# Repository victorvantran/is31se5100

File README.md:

# is31se5100
Interfacing multiple is31se5100 with multiple max7301 daisy-chained
Testing different electrodes

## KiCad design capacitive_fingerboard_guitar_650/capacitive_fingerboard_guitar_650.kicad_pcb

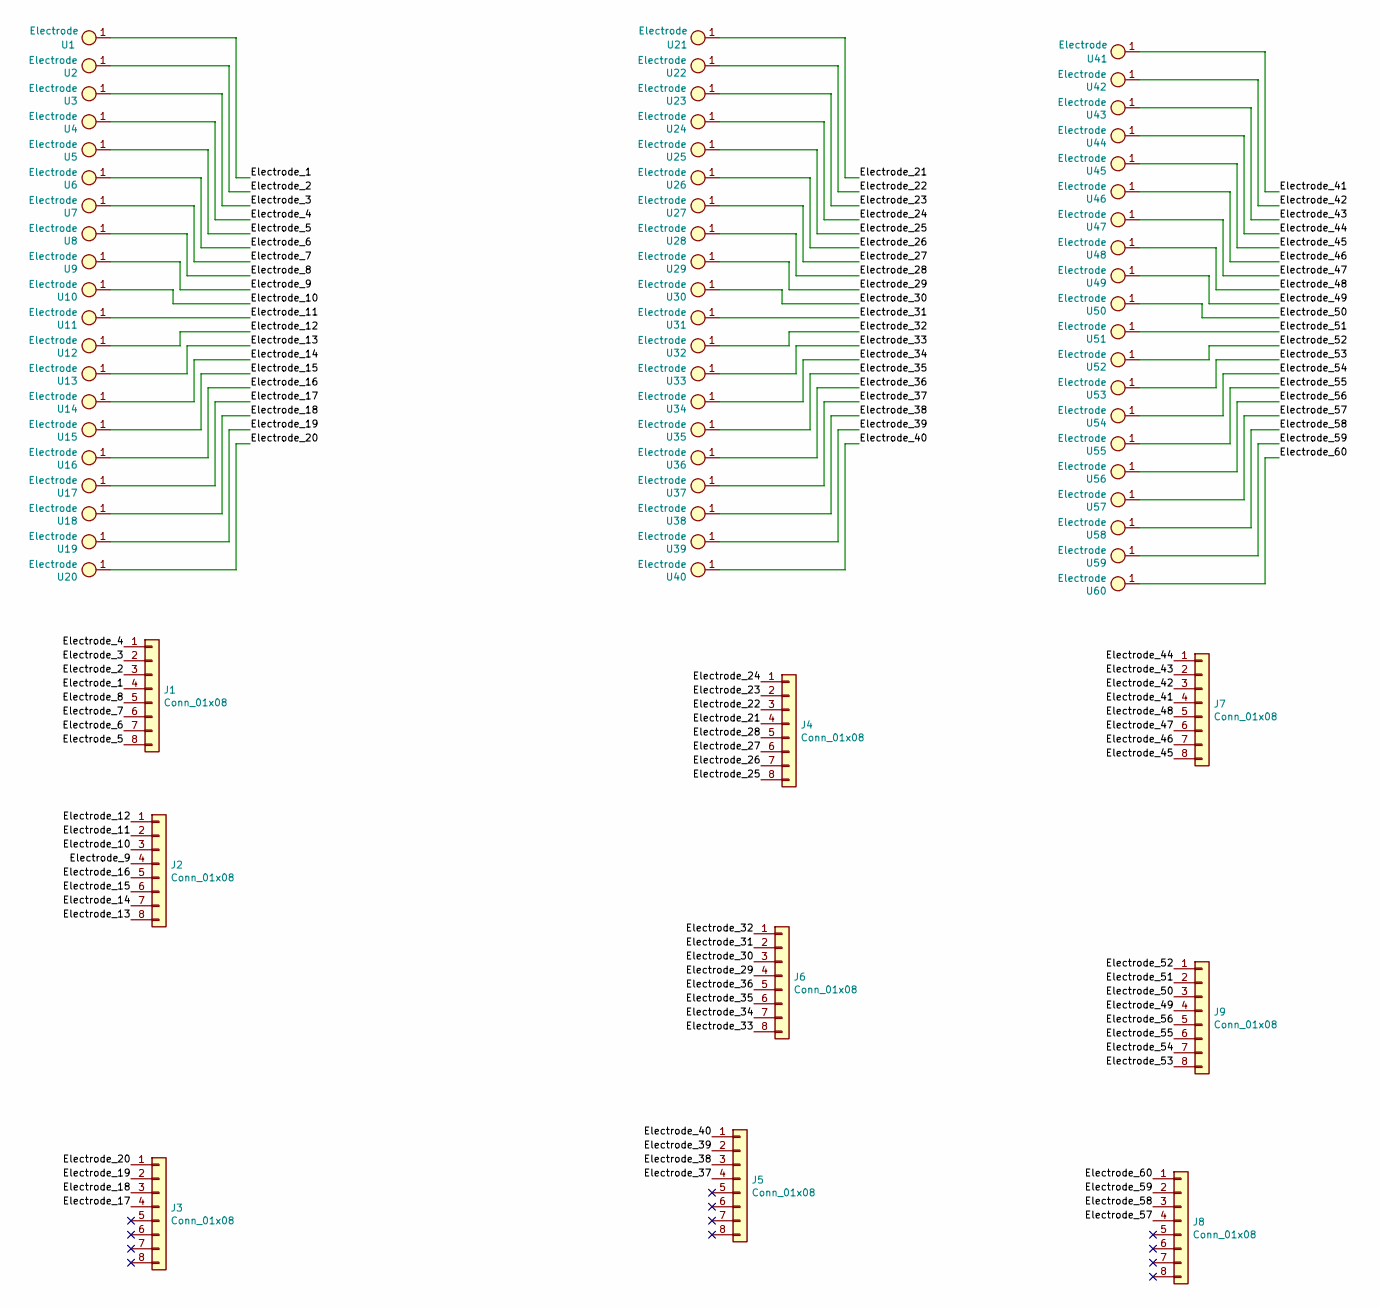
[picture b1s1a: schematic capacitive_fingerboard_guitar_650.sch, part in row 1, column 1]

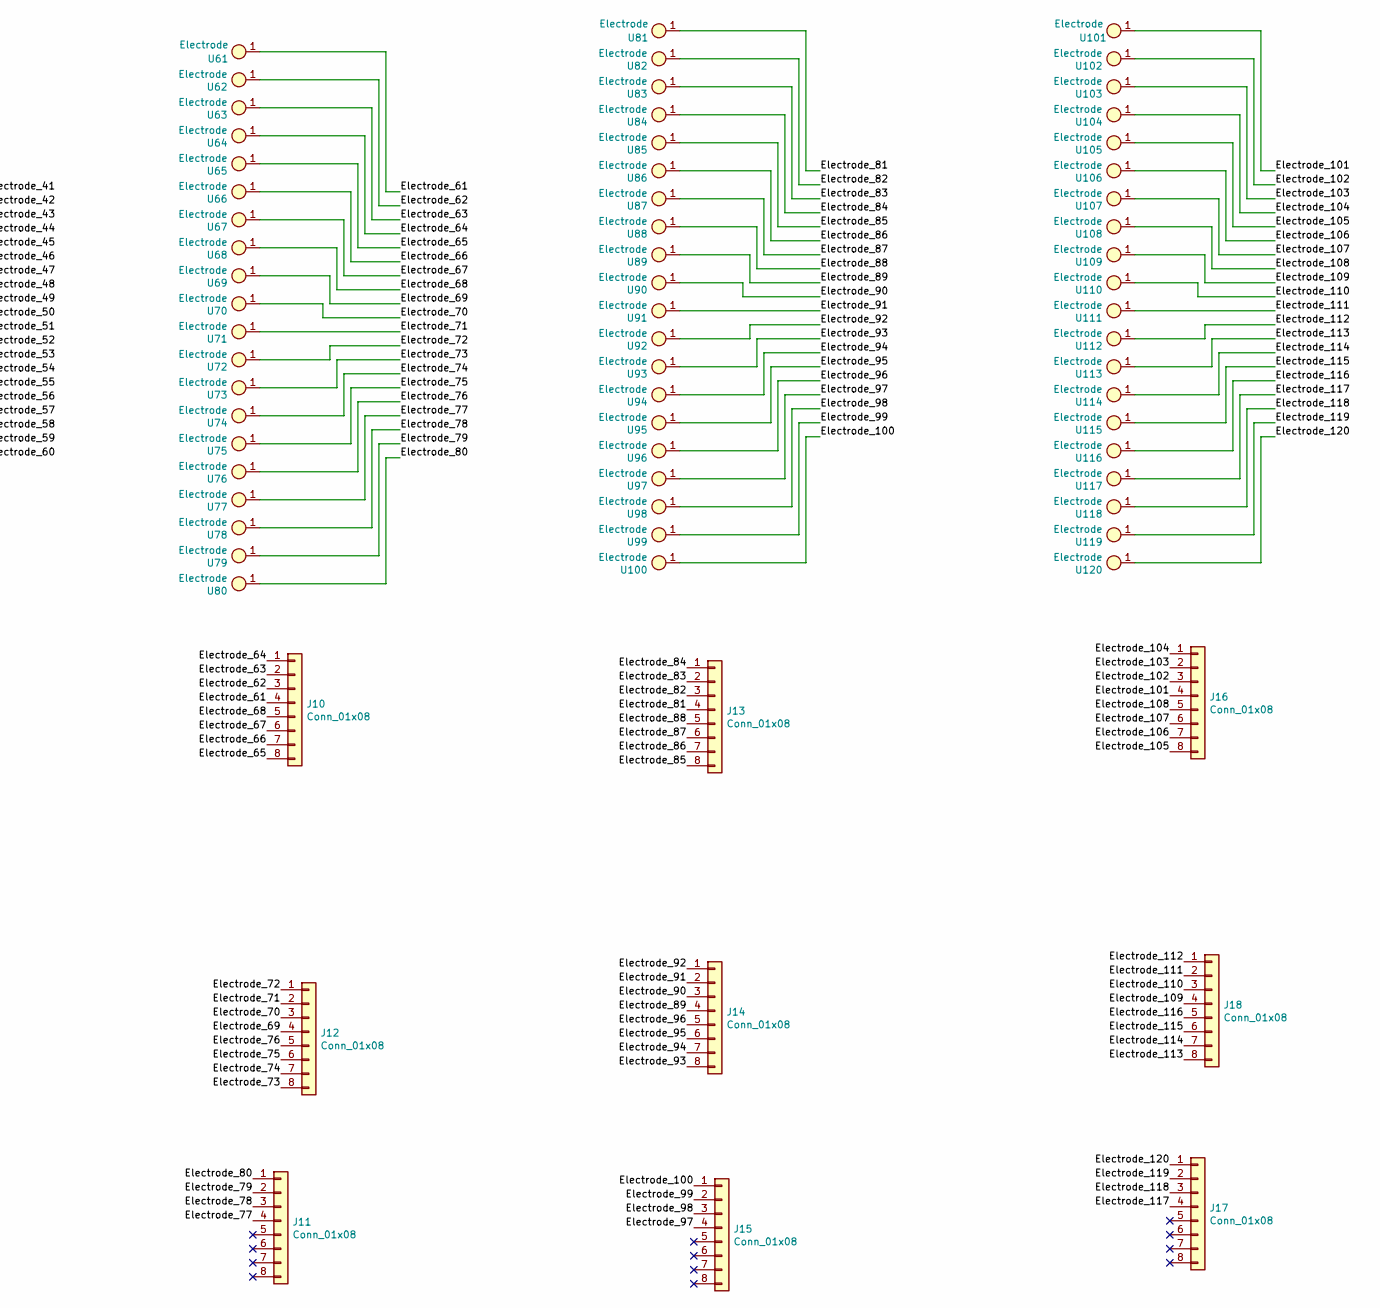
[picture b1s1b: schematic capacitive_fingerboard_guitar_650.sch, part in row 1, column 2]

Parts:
J1, J2, J3, J4, J5, J6, J7, J8, J9, J10, J11, J12, J13, J14, J15, J16, J17, J18: Conn_01x08; SAMTEC_TSM-108-01-F-SV
U1: Electrode; E2_F2
U2: Electrode; E2_F#2
U3: Electrode; E2_G2
U4: Electrode; E2_G#2
U5: Electrode; E2_A2
U6: Electrode; E2_A#2
U7: Electrode; E2_B2
U8: Electrode; E2_C3
U9: Electrode; E2_C#3
U10: Electrode; E2_D3
U11: Electrode; E2_D#3
U12: Electrode; E2_E3
U13: Electrode; E2_F3
U14: Electrode; E2_F#3
U15: Electrode; E2_G3
U16: Electrode; E2_G#3
U17: Electrode; E2_A3
U18: Electrode; E2_A#3
U19: Electrode; E2_B3
U20: Electrode; E2_C4
U21: Electrode; A2_A#2
U22: Electrode; A2_B2
U23: Electrode; A2_C3
U24: Electrode; A2_C#3
U25: Electrode; A2_D3
U26: Electrode; A2_D#3
U27: Electrode; A2_E3
U28: Electrode; A2_F3
U29: Electrode; A2_F#3
U30: Electrode; A2_G3
U31: Electrode; A2_G#3
U32: Electrode; A2_A3
U33: Electrode; A2_A#3
U34: Electrode; A2_B3
U35: Electrode; A2_C4
U36: Electrode; A2_C#4
U37: Electrode; A2_D4
U38: Electrode; A2_D#4
U39: Electrode; A2_E4
U40: Electrode; A2_F4
U41: Electrode; D3_D#3
U42: Electrode; D3_E3
U43: Electrode; D3_F3
U44: Electrode; D3_F#3
U45: Electrode; D3_G3
U46: Electrode; D3_G#3
U47: Electrode; D3_A3
U48: Electrode; D3_A#3
U49: Electrode; D3_B3
U50: Electrode; D3_C4
U51: Electrode; D3_C#4
U52: Electrode; D3_D4
U53: Electrode; D3_D#4
U54: Electrode; D3_E4
U55: Electrode; D3_F4
U56: Electrode; D3_F#4
U57: Electrode; D3_G4
U58: Electrode; D3_G#4
U59: Electrode; D3_A4
U60: Electrode; D3_A#4
U61: Electrode; G3_G#3
U62: Electrode; G3_A3
U63: Electrode; G3_A#3
U64: Electrode; G3_B3
U65: Electrode; G3_C4
U66: Electrode; G3_C#4
U67: Electrode; G3_D4
U68: Electrode; G3_D#4
U69: Electrode; G3_E4
U70: Electrode; G3_F4
U71: Electrode; G3_F#4
U72: Electrode; G3_G4
U73: Electrode; G3_G#4
U74: Electrode; G3_A4
U75: Electrode; G3_A#4
U76: Electrode; G3_B4
U77: Electrode; G3_C5
U78: Electrode; G3_C#5
U79: Electrode; G3_D5
U80: Electrode; G3_D#5
U81: Electrode; B3_C4
U82: Electrode; B3_C#4
U83: Electrode; B3_D4
U84: Electrode; B3_D#4
U85: Electrode; B3_E4
U86: Electrode; B3_F4
U87: Electrode; B3_F#4
U88: Electrode; B3_G4
U89: Electrode; B3_G#4
U90: Electrode; B3_A4
U91: Electrode; B3_A#4
U92: Electrode; B3_B4
U93: Electrode; B3_C5
U94: Electrode; B3_C#5
U95: Electrode; B3_D5
U96: Electrode; B3_D#5
U97: Electrode; B3_E5
U98: Electrode; B3_F5
U99: Electrode; B3_F#5
U100: Electrode; B3_G5
U101: Electrode; E4_F4
U102: Electrode; E4_F#4
U103: Electrode; E4_G4
U104: Electrode; E4_G#4
U105: Electrode; E4_A4
U106: Electrode; E4_A#4
U107: Electrode; E4_B4
U108: Electrode; E4_C5
U109: Electrode; E4_C#5
U110: Electrode; E4_D5
U111: Electrode; E4_D#5
U112: Electrode; E4_E5
U113: Electrode; E4_F5
U114: Electrode; E4_F#5
U115: Electrode; E4_G5
U116: Electrode; E4_G#5
U117: Electrode; E4_A5
U118: Electrode; E4_A#5
U119: Electrode; E4_B5
U120: Electrode; E4_C6

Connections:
/Electrode_1: J1.4, U1.1
/Electrode_2: J1.3, U2.1
/Electrode_3: J1.2, U3.1
/Electrode_4: J1.1, U4.1
/Electrode_5: J1.8, U5.1
/Electrode_6: J1.7, U6.1
/Electrode_7: J1.6, U7.1
/Electrode_8: J1.5, U8.1
/Electrode_9: J2.4, U9.1
/Electrode_10: J2.3, U10.1
/Electrode_11: J2.2, U11.1
/Electrode_12: J2.1, U12.1
/Electrode_13: J2.8, U13.1
/Electrode_14: J2.7, U14.1
/Electrode_15: J2.6, U15.1
/Electrode_16: J2.5, U16.1
/Electrode_17: J3.4, U17.1
/Electrode_18: J3.3, U18.1
/Electrode_19: J3.2, U19.1
/Electrode_20: J3.1, U20.1
/Electrode_21: J4.4, U21.1
/Electrode_22: J4.3, U22.1
/Electrode_23: J4.2, U23.1
/Electrode_24: J4.1, U24.1
/Electrode_25: J4.8, U25.1
/Electrode_26: J4.7, U26.1
/Electrode_27: J4.6, U27.1
/Electrode_28: J4.5, U28.1
/Electrode_29: J6.4, U29.1
/Electrode_30: J6.3, U30.1
/Electrode_31: J6.2, U31.1
/Electrode_32: J6.1, U32.1
/Electrode_33: J6.8, U33.1
/Electrode_34: J6.7, U34.1
/Electrode_35: J6.6, U35.1
/Electrode_36: J6.5, U36.1
/Electrode_37: J5.4, U37.1
/Electrode_38: J5.3, U38.1
/Electrode_39: J5.2, U39.1
/Electrode_40: J5.1, U40.1
/Electrode_41: J7.4, U41.1
/Electrode_42: J7.3, U42.1
/Electrode_43: J7.2, U43.1
/Electrode_44: J7.1, U44.1
/Electrode_45: J7.8, U45.1
/Electrode_46: J7.7, U46.1
/Electrode_47: J7.6, U47.1
/Electrode_48: J7.5, U48.1
/Electrode_49: J9.4, U49.1
/Electrode_50: J9.3, U50.1
/Electrode_51: J9.2, U51.1
/Electrode_52: J9.1, U52.1
/Electrode_53: J9.8, U53.1
/Electrode_54: J9.7, U54.1
/Electrode_55: J9.6, U55.1
/Electrode_56: J9.5, U56.1
/Electrode_57: J8.4, U57.1
/Electrode_58: J8.3, U58.1
/Electrode_59: J8.2, U59.1
/Electrode_60: J8.1, U60.1
/Electrode_61: J10.4, U61.1
/Electrode_62: J10.3, U62.1
/Electrode_63: J10.2, U63.1
/Electrode_64: J10.1, U64.1
/Electrode_65: J10.8, U65.1
/Electrode_66: J10.7, U66.1
/Electrode_67: J10.6, U67.1
/Electrode_68: J10.5, U68.1
/Electrode_69: J12.4, U69.1
/Electrode_70: J12.3, U70.1
/Electrode_71: J12.2, U71.1
/Electrode_72: J12.1, U72.1
/Electrode_73: J12.8, U73.1
/Electrode_74: J12.7, U74.1
/Electrode_75: J12.6, U75.1
/Electrode_76: J12.5, U76.1
/Electrode_77: J11.4, U77.1
/Electrode_78: J11.3, U78.1
/Electrode_79: J11.2, U79.1
/Electrode_80: J11.1, U80.1
/Electrode_81: J13.4, U81.1
/Electrode_82: J13.3, U82.1
/Electrode_83: J13.2, U83.1
/Electrode_84: J13.1, U84.1
/Electrode_85: J13.8, U85.1
/Electrode_86: J13.7, U86.1
/Electrode_87: J13.6, U87.1
/Electrode_88: J13.5, U88.1
/Electrode_89: J14.4, U89.1
/Electrode_90: J14.3, U90.1
/Electrode_91: J14.2, U91.1
/Electrode_92: J14.1, U92.1
/Electrode_93: J14.8, U93.1
/Electrode_94: J14.7, U94.1
/Electrode_95: J14.6, U95.1
/Electrode_96: J14.5, U96.1
/Electrode_97: J15.4, U97.1
/Electrode_98: J15.3, U98.1
/Electrode_99: J15.2, U99.1
/Electrode_100: J15.1, U100.1
/Electrode_101: J16.4, U101.1
/Electrode_102: J16.3, U102.1
/Electrode_103: J16.2, U103.1
/Electrode_104: J16.1, U104.1
/Electrode_105: J16.8, U105.1
/Electrode_106: J16.7, U106.1
/Electrode_107: J16.6, U107.1
/Electrode_108: J16.5, U108.1
/Electrode_109: J18.4, U109.1
/Electrode_110: J18.3, U110.1
/Electrode_111: J18.2, U111.1
/Electrode_112: J18.1, U112.1
/Electrode_113: J18.8, U113.1
/Electrode_114: J18.7, U114.1
/Electrode_115: J18.6, U115.1
/Electrode_116: J18.5, U116.1
/Electrode_117: J17.4, U117.1
/Electrode_118: J17.3, U118.1
/Electrode_119: J17.2, U119.1
/Electrode_120: J17.1, U120.1

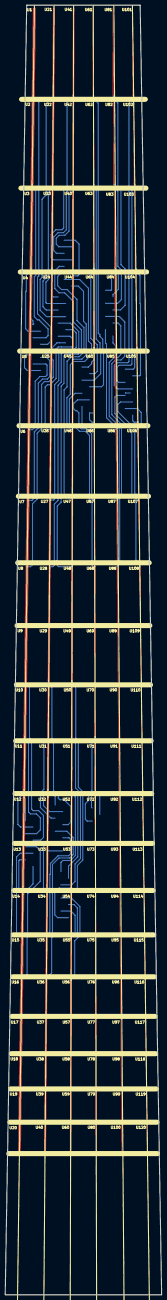
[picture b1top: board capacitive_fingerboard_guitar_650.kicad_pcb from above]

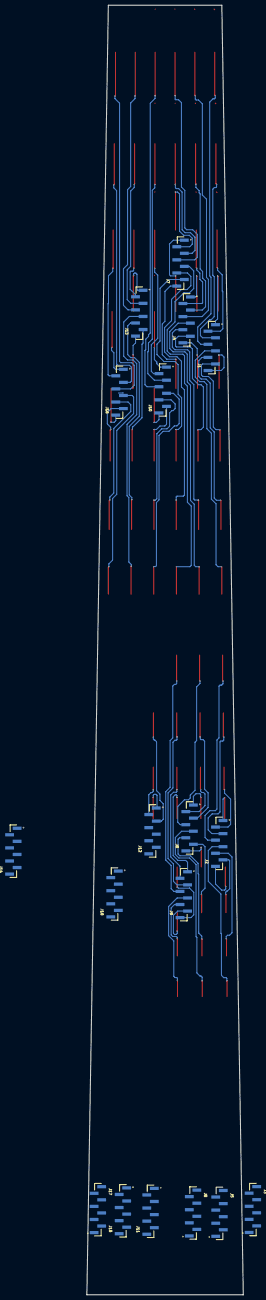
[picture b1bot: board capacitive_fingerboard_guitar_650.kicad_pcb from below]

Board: 4 copper layers, 60.6 x 500.0 mm, 138 parts (18 on the bottom side), 120 nets.

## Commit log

2021-09-13 Added buttons to schematic
2021-09-18 Added connections to IS31SE5100 and daisy-linked MAX7301s
2021-09-18 Added control test
2021-09-18 Simplified by reducing number of IS31SE5100
2021-09-18 Added pull-ups for I2C and INTB
2021-09-18 Preparation for power
2021-09-20 Added power circuit and extraneous parts
2021-09-20 Simplified by removing one more is31se5100
2021-09-20 Building footprints for electrodes
2021-09-25 Prepare part list
2021-09-25 Changed i2c pins to open collector
2021-09-25 Added more debug jumpers to test the open drain of INTB pins of IS31SE5100
2021-09-26 Confirmed schematic
2021-09-26 Rename schematic parts
2021-09-26 Matched footprints for main parts
2021-10-06 Pre split
2021-10-08 Established is31se5100_tinker
2021-10-08 Established is31se5100_chained
2021-10-25 Added guitar fingerboard beginnings
2021-10-28 Added frets on E2 string
2021-10-29 Added more frets on pcb
2021-10-30 Added all frets on pcb
2021-10-30 Tracing is31se5100
2021-10-31 Added traces for the first third
2021-10-31 Added missing trace
2021-10-31 Over 50% trace done
